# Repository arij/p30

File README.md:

# Pendulum 30

A 30% compact keyboard with layers

# Layouts
1:

2:

# Firmware
The Pendulum 30 uses QMK for its firmware which can be found here: https://github.com/qmk/qmk_firmware/

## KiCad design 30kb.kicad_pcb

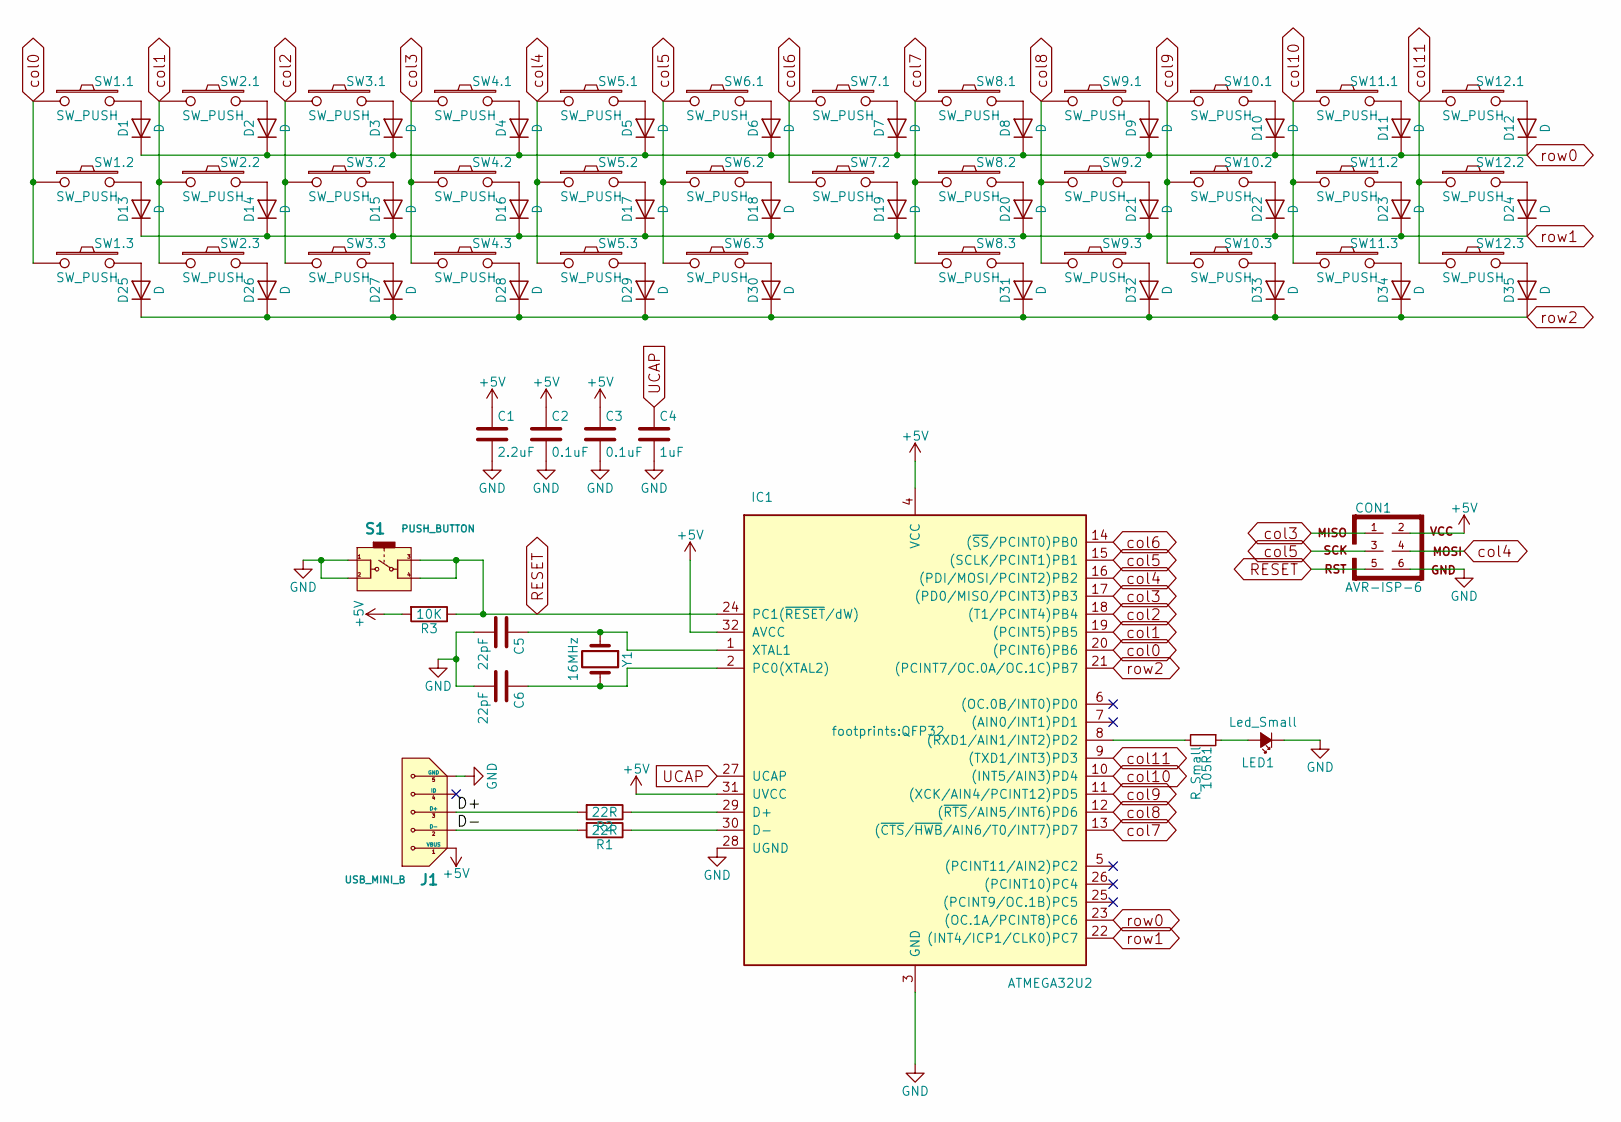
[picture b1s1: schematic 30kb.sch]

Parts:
105R1: R_Small; R_0805
C1: 2.2uF; C_0805
C2, C3: 0.1uF; C_0603
C4: 1uF; C_0805
C5, C6: 22pF; C_0603
CON1: AVR-ISP-6
D1, D2, D3, D4, D5, D6, D7, D8, D9, D10, D11, D12, D13, D14, D15, D16, D17, D18, D19, D20, D21, D22, D23, D24, D25, D26, D27, D28, D29, D30, D31, D32, D33, D34, D35: D; SOD-123
IC1: ATMEGA32U2; QFP32
J1: USB_MINI_B; 72f6-usb_mini_b_hiroseux60sc-mb-5s8
LED1: Led_Small; LED_0805
R1, R2: 22R; R_0805
R3: 10K; R_0805
S1: PUSH_BUTTON; PUSH_BUTTON_PTS645SM43SMTR92LFS
SW1.1, SW1.2, SW1.3, SW2.1, SW2.2, SW2.3, SW3.1, SW3.2, SW3.3, SW4.1, SW4.2, SW4.3, SW5.1, SW5.2, SW5.3, SW6.1, SW6.2, SW7.1, SW7.2, SW8.1, SW8.2, SW8.3, SW9.1, SW9.2, SW9.3, SW10.1, SW10.2, SW10.3, SW11.1, SW11.2, SW11.3, SW12.1, SW12.2, SW12.3: SW_PUSH; CHERRY_PCB_100H
SW6.3: SW_PUSH; CHERRY_PCB_200H
Y1: 16MHz; crystal_ABLS7M

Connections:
+5V: C1.1, C2.1, C3.1, CON1.2, IC1.4 (VCC), IC1.31 (UVCC), IC1.32 (AVCC), J1.1 (VBUS), R3.2
/D+: J1.3 (D+), R2.2
/D-: J1.2 (D-), R1.2
GND: C1.2, C2.2, C3.2, C4.2, C5.2, C6.2, CON1.6, IC1.3 (GND), IC1.28 (UGND), J1.5 (GND), LED1.1 (K), S1.1, S1.2
unnamed: 105R1.1, LED1.2 (A)
unnamed: 105R1.2, IC1.8 ((RXD1/AIN1/INT2)PD2)
unnamed: C5.1, IC1.1 (XTAL1), Y1.1
unnamed: C6.1, IC1.2 (PC0(XTAL2)), Y1.2
unnamed: D1.2 (A), SW1.1.2
unnamed: D2.2 (A), SW2.1.2
unnamed: D3.2 (A), SW3.1.2
unnamed: D4.2 (A), SW4.1.2
unnamed: D5.2 (A), SW5.1.2
unnamed: D6.2 (A), SW6.1.2
unnamed: D7.2 (A), SW7.1.2
unnamed: D8.2 (A), SW8.1.2
unnamed: D9.2 (A), SW9.1.2
unnamed: D10.2 (A), SW10.1.2
unnamed: D11.2 (A), SW11.1.2
unnamed: D12.2 (A), SW12.1.2
unnamed: D13.2 (A), SW1.2.2
unnamed: D14.2 (A), SW2.2.2
unnamed: D15.2 (A), SW3.2.2
unnamed: D16.2 (A), SW4.2.2
unnamed: D17.2 (A), SW5.2.2
unnamed: D18.2 (A), SW6.2.2
unnamed: D19.2 (A), SW7.2.2
unnamed: D20.2 (A), SW8.2.2
unnamed: D21.2 (A), SW9.2.2
unnamed: D22.2 (A), SW10.2.2
unnamed: D23.2 (A), SW11.2.2
unnamed: D24.2 (A), SW12.2.2
unnamed: D25.2 (A), SW1.3.2
unnamed: D26.2 (A), SW2.3.2
unnamed: D27.2 (A), SW3.3.2
unnamed: D28.2 (A), SW4.3.2
unnamed: D29.2 (A), SW5.3.2
unnamed: D30.2 (A), SW6.3.2
unnamed: D31.2 (A), SW8.3.2
unnamed: D32.2 (A), SW9.3.2
unnamed: D33.2 (A), SW10.3.2
unnamed: D34.2 (A), SW11.3.2
unnamed: D35.2 (A), SW12.3.2
unnamed: IC1.29 (D+), R2.1
unnamed: IC1.30 (D-), R1.1
RESET: CON1.5, IC1.24 (PC1(~RESET~/dW)), R3.1, S1.3, S1.4
UCAP: C4.1, IC1.27 (UCAP)
col0: IC1.20 ((PCINT6)PB6), SW1.1.1, SW1.2.1, SW1.3.1
col1: IC1.19 ((PCINT5)PB5), SW2.1.1, SW2.2.1, SW2.3.1
col2: IC1.18 ((T1/PCINT4)PB4), SW3.1.1, SW3.2.1, SW3.3.1
col3: CON1.1, IC1.17 ((PD0/MISO/PCINT3)PB3), SW4.1.1, SW4.2.1, SW4.3.1
col4: CON1.4, IC1.16 ((PDI/MOSI/PCINT2)PB2), SW5.1.1, SW5.2.1, SW5.3.1
col5: CON1.3, IC1.15 ((SCLK/PCINT1)PB1), SW6.1.1, SW6.2.1, SW6.3.1
col6: IC1.14 ((~SS~/PCINT0)PB0), SW7.1.1, SW7.2.1
col7: IC1.13 ((~CTS~/~HWB~/AIN6/T0/INT7)PD7), SW8.1.1, SW8.2.1, SW8.3.1
col8: IC1.12 ((~RTS~/AIN5/INT6)PD6), SW9.1.1, SW9.2.1, SW9.3.1
col9: IC1.11 ((XCK/AIN4/PCINT12)PD5), SW10.1.1, SW10.2.1, SW10.3.1
col10: IC1.10 ((INT5/AIN3)PD4), SW11.1.1, SW11.2.1, SW11.3.1
col11: IC1.9 ((TXD1/INT3)PD3), SW12.1.1, SW12.2.1, SW12.3.1
row0: D1.1 (K), D2.1 (K), D3.1 (K), D4.1 (K), D5.1 (K), D6.1 (K), D7.1 (K), D8.1 (K), D9.1 (K), D10.1 (K), D11.1 (K), D12.1 (K), IC1.23 ((OC.1A/PCINT8)PC6)
row1: D13.1 (K), D14.1 (K), D15.1 (K), D16.1 (K), D17.1 (K), D18.1 (K), D19.1 (K), D20.1 (K), D21.1 (K), D22.1 (K), D23.1 (K), D24.1 (K), IC1.22 ((INT4/ICP1/CLK0)PC7)
row2: D25.1 (K), D26.1 (K), D27.1 (K), D28.1 (K), D29.1 (K), D30.1 (K), D31.1 (K), D32.1 (K), D33.1 (K), D34.1 (K), D35.1 (K), IC1.21 ((PCINT7/OC.0A/OC.1C)PB7)

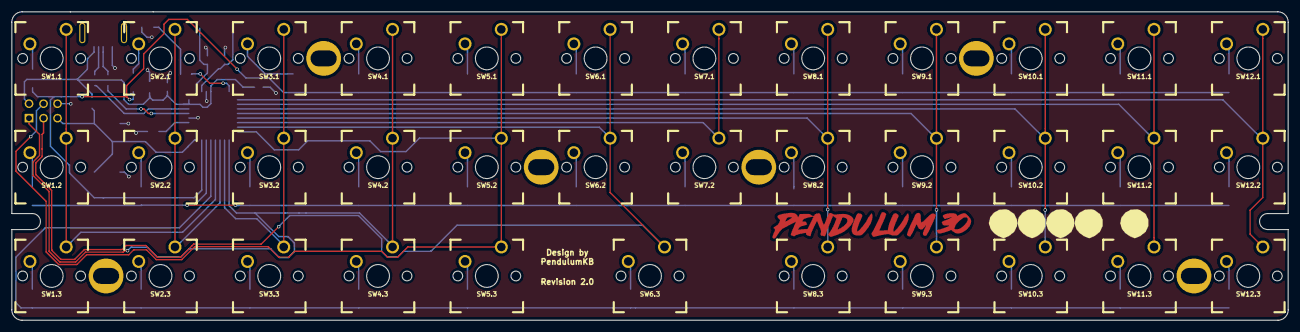
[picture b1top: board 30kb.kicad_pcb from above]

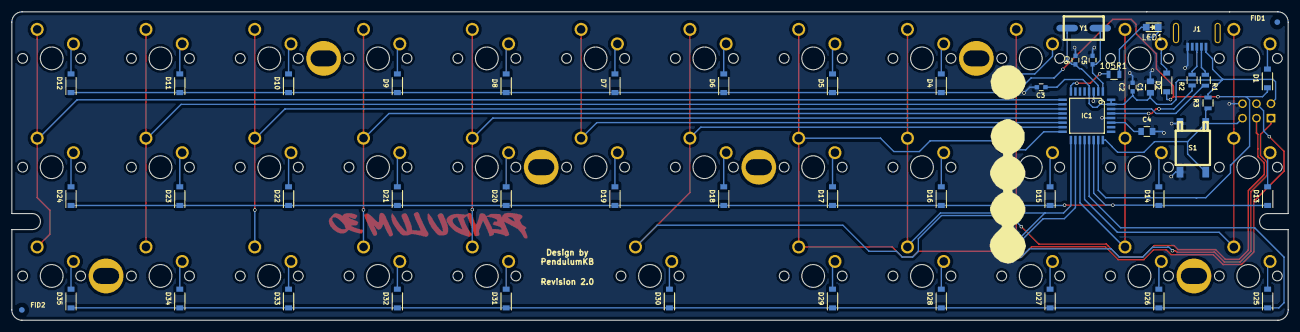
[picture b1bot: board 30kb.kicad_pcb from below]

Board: 2 copper layers, 223.5 x 54.0 mm, 94 parts (52 on the bottom side), 62 nets.

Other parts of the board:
FID1, FID2: Fiducial_1mm_Dia_2.54mm_Outer_CopperTop
POKER_OVAL_HOLE: >VALUE; POKER_OVAL_HOLE
POKER_OVAL_HOLE#2, POKER_OVAL_HOLE#3, POKER_OVAL_HOLE#4, POKER_OVAL_HOLE#5, POKER_OVAL_HOLE#6: >VALUE; POKER_OVAL_HOLE

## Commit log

2017-03-11 :circus_tent: Added .gitattributes & .gitignore files
2017-03-11 Kicad files
2017-03-25 License
